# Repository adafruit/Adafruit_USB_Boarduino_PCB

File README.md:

# USB Boarduino (Arduino compatible) Kit w/ATmega328 - v2.0

If you've ever struggled to use a solderless breadboard with an Arduino, you understand how frustrating it can be!

This development board acts just like an Arduino, and works with the latest Arduino software. For many projects it can even be preferable! The kit includes all parts necessary, the assembly is straightforward and well documented, using just a soldering iron anyone can complete it within 10 or 15 minutes.

This version of the Boarduino does not have a DC jack. That means you __can't__ use a 9V adapter or battery holder with it (unless you build a 5V power supply). However __it does have USB built in__ and you can power your project or USB or by using a [Mintyboost kit](https://www.adafruit.com/products/14) (which takes 2 AA batteries).

Specifications:

- Designed to plug into a breadboard for easy prototyping
- Petite size, only 2.75" x 0.8" (75mm x 20mm)
- All 'standard' pins are brought out - Digital 0-13, Analog 0-5, ARef, 5V, 3V, Ground, and Reset
- Chip comes pre-programmed with a "no-wait" Arduino bootloader ([Read more here](https://learn.adafruit.com/arduino-tips-tricks-and-techniques/bootloader))
- 4 LEDs! There's a green power-good LED, a red "pin 13" LED (just like the Arduino), and a pair of RX and TX indicator LEDs for debugging the serial connection
- Nearly-all-surfacemount design. We left the chip as through-hole to make it easier to upgrade and repair. All surface mount parts are pre-assembled and tested.
- Reset button
- ATmega328P, running at 16.00 MHz, just like all Arduinos
- 6-pin standard ICSP header
- USB miniB jack
- 500mA fuse protects your computer's USB port from overcurrent
- Auto-reset capability

There's a lot more to read at the [USB Boarduino webpage](https://learn.adafruit.com/boarduino-kits).

### License

Adafruit invests time and resources providing this open source design, please support Adafruit and open-source hardware by purchasing products from [Adafruit](https://www.adafruit.com)!

Designed by Limor Fried/Ladyada for Adafruit Industries.

Creative Commons Attribution/Share-Alike, all text above must be included in any redistribution. See license.txt for additional details.

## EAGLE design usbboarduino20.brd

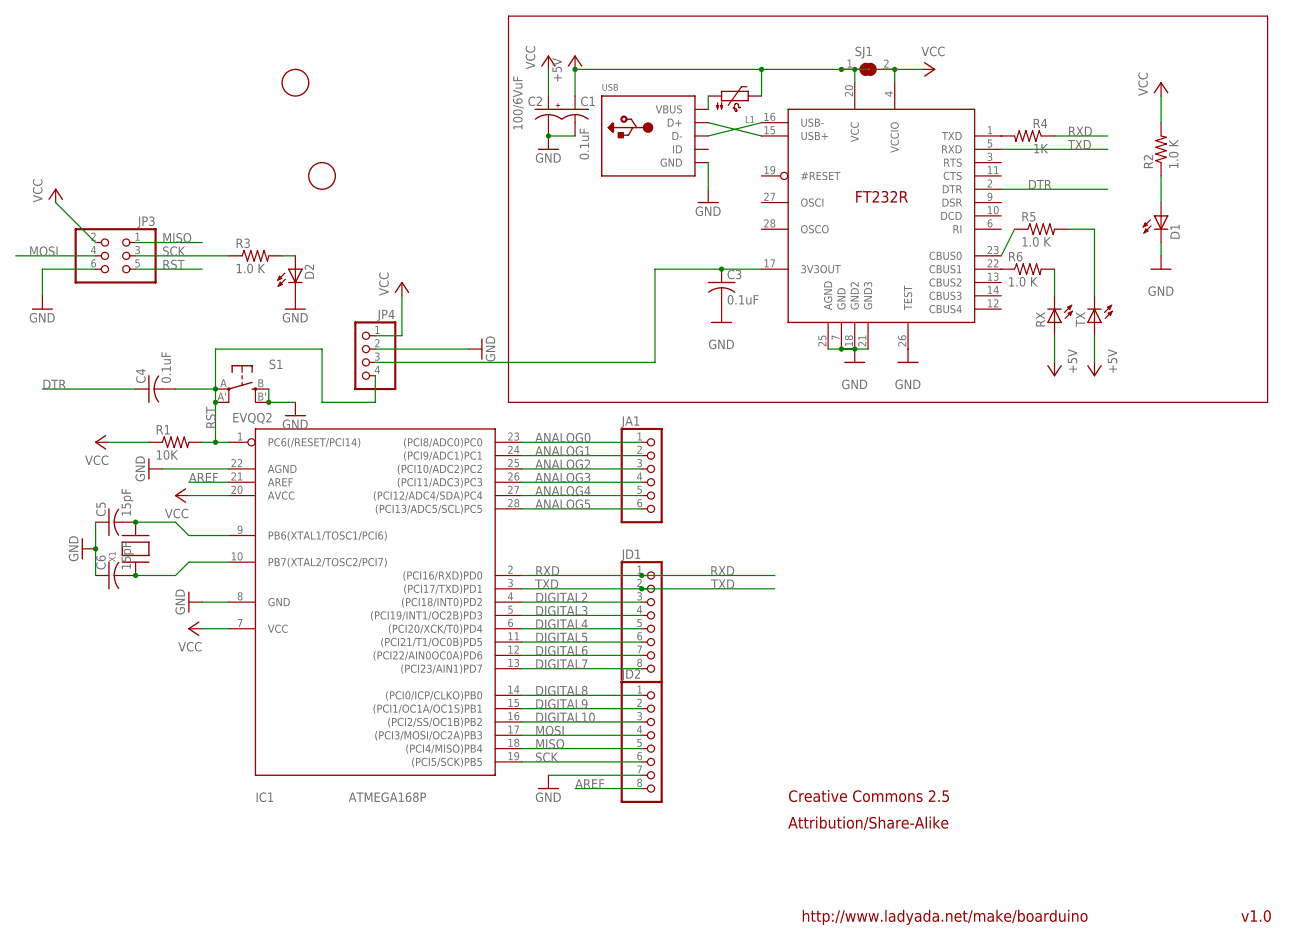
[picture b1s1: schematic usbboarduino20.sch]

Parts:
C1, C3, C4: 0.1uF; C0805K
C2: 100/6VuF; B/3528-21R
C5, C6: 15pF; C0805K
D1: LEDCHIPLED_0805; CHIPLED_0805
D2: Green; CHIPLED_0805
IC1: ATMEGA168P; DIL28/3
IC2: FT232R; TSSOP28
JA1: PINHD-1X6CB; 1X06-CLEANBIG
JD1, JD2: PINHD-1X8CLEANBIG; 1X08-CLEANBIG
JP3: PINHD-2X3; 2X03
JP4: PINHD-1X4CB; 1X04-CB
L1: PTC1206; 1206
R1: 10K; R0805
R2, R3, R5, R6: 1.0 K; R0805
R4: 1K; R0805
RX: Green; CHIPLED_0805
S1: EVQQ2; EVQ-Q2
SJ1: SOLDERJUMPERREFLOW; SOLDERJUMPER_REFLOW
TX: Green; CHIPLED_0805
U$1, U$2: FIDUCIAL; FIDUCIAL_1MM
USB: USBMINIB; USB-MINIB
X1: XTALNX5032; NX5032

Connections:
3V: C3.1, IC2.17 (3V3OUT), JP4.3
+5V: C1.1, IC2.20 (VCC), L1.2, RX.A, SJ1.1, TX.A
ANALOG0: IC1.23 ((PCI8/ADC0)PC0), JA1.1
ANALOG1: IC1.24 ((PCI9/ADC1)PC1), JA1.2
ANALOG2: IC1.25 ((PCI10/ADC2)PC2), JA1.3
ANALOG3: IC1.26 ((PCI11/ADC3)PC3), JA1.4
ANALOG4: IC1.27 ((PCI12/ADC4/SDA)PC4), JA1.5
ANALOG5: IC1.28 ((PCI13/ADC5/SCL)PC5), JA1.6
AREF: IC1.21 (AREF), JD2.8
DIGITAL2: IC1.4 ((PCI18/INT0)PD2), JD1.3
DIGITAL3: IC1.5 ((PCI19/INT1/OC2B)PD3), JD1.4
DIGITAL4: IC1.6 ((PCI20/XCK/T0)PD4), JD1.5
DIGITAL5: IC1.11 ((PCI21/T1/OC0B)PD5), JD1.6
DIGITAL6: IC1.12 ((PCI22/AIN0OC0A)PD6), JD1.7
DIGITAL7: IC1.13 ((PCI23/AIN1)PD7), JD1.8
DIGITAL8: IC1.14 ((PCI0/ICP/CLKO)PB0), JD2.1
DIGITAL9: IC1.15 ((PCI1/OC1A/OC1S)PB1), JD2.2
DIGITAL10: IC1.16 ((PCI2/SS/OC1B)PB2), JD2.3
DTR: C4.1, IC2.2 (DTR)
GND: C1.2, C2.-, C3.2, C5.1, C6.1, D1.C, D2.C, IC1.8 (GND), IC1.22 (AGND), IC2.7 (GND), IC2.18 (GND2), IC2.21 (GND3), IC2.25 (AGND), IC2.26 (TEST), JD2.7, JP3.6, JP4.2, S1.B (S), S1.B' (S1), USB.GND
MISO: IC1.18 ((PCI4/MISO)PB4), JD2.5, JP3.1
MOSI: IC1.17 ((PCI3/MOSI/OC2A)PB3), JD2.4, JP3.4
unnamed: C5.2, IC1.9 (PB6(XTAL1/TOSC1/PCI6)), X1.P$2
unnamed: C6.2, IC1.10 (PB7(XTAL2/TOSC2/PCI7)), X1.P$1
unnamed: D1.A, R2.1
unnamed: D2.A, R3.2
unnamed: IC2.15 (USB+), USB.D+
unnamed: IC2.16 (USB-), USB.D-
unnamed: IC2.1 (TXD), R4.2
unnamed: L1.1, USB.VBUS
unnamed: R6.2, RX.C
unnamed: R5.2, TX.C
unnamed: IC2.22 (CBUS1), R6.1
unnamed: IC2.23 (CBUS0), R5.1
RST: C4.2, IC1.1 (PC6(/RESET/PCI14)), JP3.5, JP4.4, R1.2, S1.A, S1.A' (P1)
RXD: IC1.2 ((PCI16/RXD)PD0), JD1.1, R4.1
SCK: IC1.19 ((PCI5/SCK)PB5), JD2.6, JP3.3, R3.1
TXD: IC1.3 ((PCI17/TXD)PD1), IC2.5 (RXD), JD1.2
VCC: C2.+, IC1.7 (VCC), IC1.20 (AVCC), IC2.4 (VCCIO), JP3.2, JP4.1, R1.1, R2.2, SJ1.2

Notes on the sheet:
v1.0
http://www.ladyada.net/make/boarduino
Creative Commons 2.5
Attribution/Share-Alike

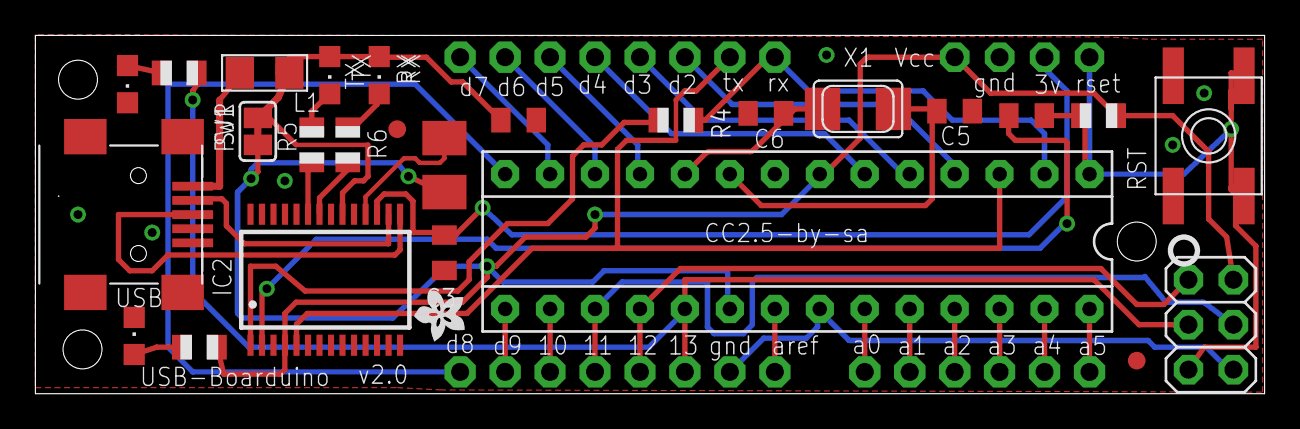
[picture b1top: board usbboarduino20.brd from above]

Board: 2 copper layers, 69.4 x 20.2 mm, 31 parts (0 on the bottom side), 39 nets.

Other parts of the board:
U$3: ADAFRUIT200MIL

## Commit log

2010-10-30 Added image and cleaned up sch a little
2019-03-28 readme + image
2026-06-03 update file format to XML
